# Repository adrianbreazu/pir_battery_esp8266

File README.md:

# pir_battery_esp8266

#About

This is a simple ESP8266-01 project that activates every time a detection is valid and sends a POST request.

#Hardware requirements

* ESP8266-01
* 3 capacitors (1000uF, 2 x 1 uF)
* MCP1700 3.3 voltage regulator LDO
* 2 resistors (550R, 10K)
* 1 pir sensor
* 1 2n2222A transistor
* pcb board and connectors

# Software requirements

* Web server
* clone this repository
* Arduino IDE and ESP8266 board added

#Images

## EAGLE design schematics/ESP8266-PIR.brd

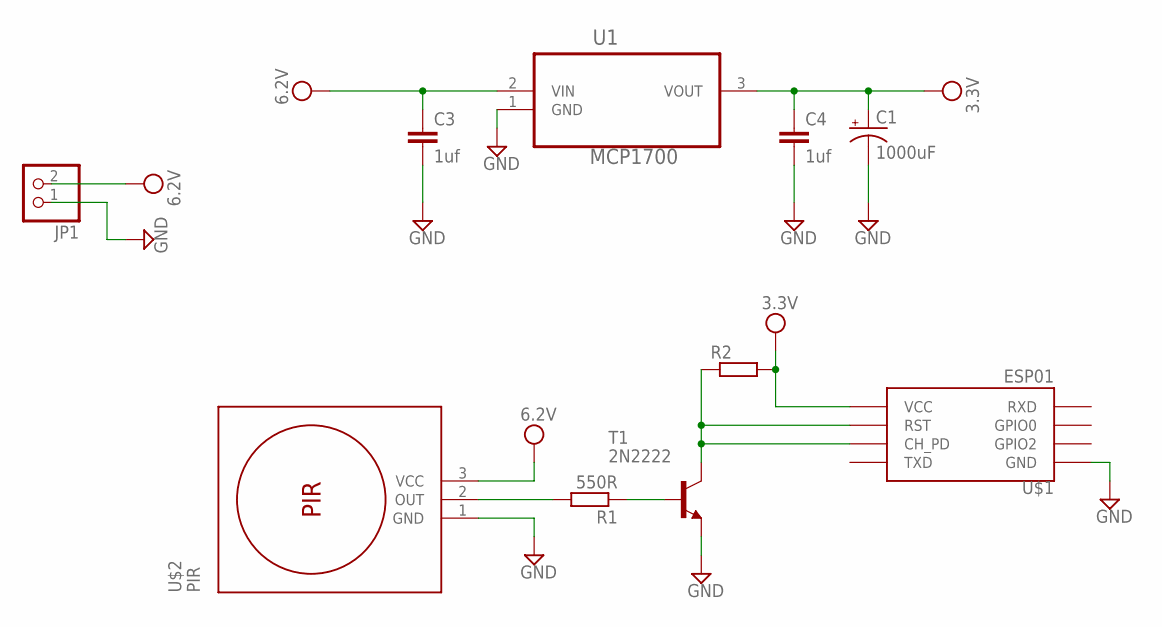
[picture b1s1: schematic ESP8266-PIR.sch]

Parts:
C1: 1000uF; CPOL-RADIAL-1000UF-25V
C3, C4: 1uf; CAP-PTH-SMALLEZ
JP1: PINHD-1X2; 1X02
R1: 550R; 0207/15
R2: R-EU_0207/15; 0207/15
T1: 2N2222; TO18
U1: MCP1700; TO127P254X495-3
U$1: ESP01
U$2: PIR; MOTION-PIR-DYP-ME003

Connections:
3.3V: C1.+, C4.1, R2.2, U1.3 (VOUT), U$1.VCC
3.3V_R: R2.1, T1.3 (C), U$1.CH_PD, U$1.RST
6.2V: C3.1, JP1.2, U1.2 (VIN), U$2.3 (VCC)
GND: C1.-, C3.2, C4.2, JP1.1, T1.1 (E), U1.1 (GND), U$1.GND, U$2.1 (GND)
OUT: R1.2, U$2.2 (OUT)
OUT_R: R1.1, T1.2 (B)

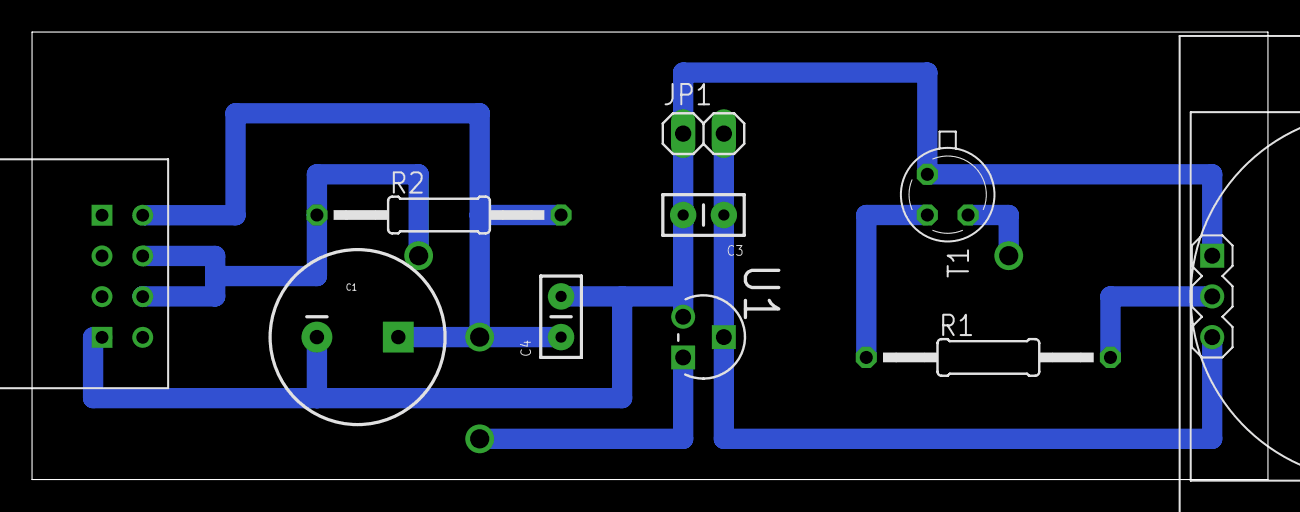
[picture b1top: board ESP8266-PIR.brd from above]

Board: 2 copper layers, 77.1 x 27.9 mm, 10 parts (0 on the bottom side), 6 nets.

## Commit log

2018-07-18 code
2018-07-18 schematics
2018-07-18 pics and readme

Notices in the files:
parts and their libraries:
diy-modules: Released under the Creative Commons Attribution 4.0 International License: http://creativecommons.org/licenses/by/4.0
SparkFun-Capacitors: Licensing: Creative Commons ShareAlike 4.0 International - https://creativecommons.org/licenses/by-sa/4.0
